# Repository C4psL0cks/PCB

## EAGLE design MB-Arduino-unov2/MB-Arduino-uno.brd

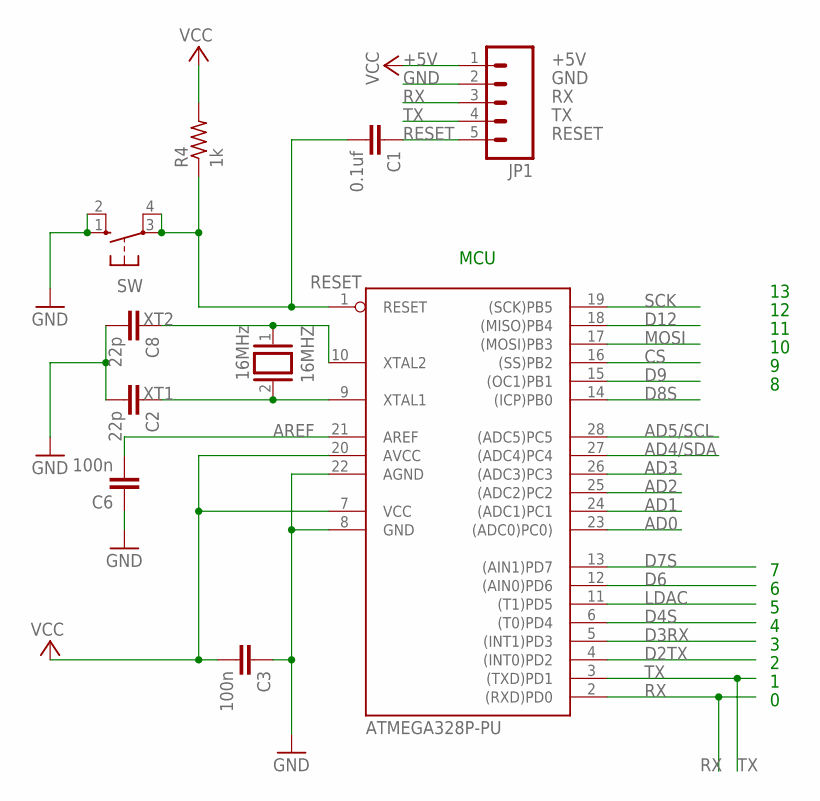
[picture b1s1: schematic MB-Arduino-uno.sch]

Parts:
16MHZ: 16MHz; QS
C1: 0.1uf; C2.5-2
C2, C8: 22p; C2.5-2
C3, C6: 100n; C2.5-2
IC: ATMEGA328P-PU; DIL28-3
JP1: M05PTH; 1X05
R4: 1k; 0204/7
SW: 10-XX; B3F-10XX

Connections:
+5V: C3.2, IC.7 (VCC), IC.20 (AVCC), JP1.1, R4.2
AD0: IC.23 ((ADC0)PC0))
AD1: IC.24 ((ADC1)PC1)
AD2: IC.25 ((ADC2)PC2)
AD3: IC.26 ((ADC3)PC3)
AD4/SDA: IC.27 ((ADC4)PC4)
AD5/SCL: IC.28 ((ADC5)PC5)
AREF: C6.2, IC.21 (AREF)
CS: IC.16 ((SS)PB2)
D2TX: IC.4 ((INT0)PD2)
D3RX: IC.5 ((INT1)PD3)
D4S: IC.6 ((T0)PD4)
D6: IC.12 ((AIN0)PD6)
D7S: IC.13 ((AIN1)PD7)
D8S: IC.14 ((ICP)PB0)
D9: IC.15 ((OC1)PB1)
D12: IC.18 ((MISO)PB4)
GND: C2.2, C3.1, C6.1, C8.2, IC.8 (GND), IC.22 (AGND), JP1.2, SW.1 (S), SW.2 (S1)
LDAC: IC.11 ((T1)PD5)
MOSI: IC.17 ((MOSI)PB3)
RESET: C1.1, C1.2, IC.1 (RESET), JP1.5, R4.1, SW.3, SW.4 (P1)
RX: IC.2 ((RXD)PD0), JP1.3
SCK: IC.19 ((SCK)PB5)
TX: IC.3 ((TXD)PD1), JP1.4
XT1: 16MHZ.2, C2.1, IC.9 (XTAL1)
XT2: 16MHZ.1, C8.1, IC.10 (XTAL2)

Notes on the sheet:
MCU

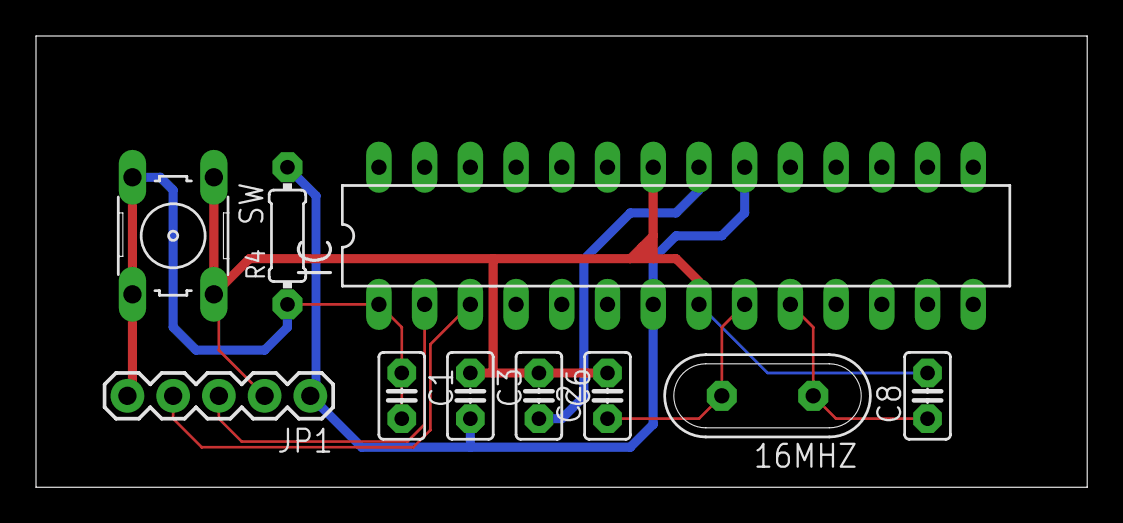
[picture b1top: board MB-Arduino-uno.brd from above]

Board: 2 copper layers, 58.4 x 25.1 mm, 10 parts (0 on the bottom side), 8 nets.

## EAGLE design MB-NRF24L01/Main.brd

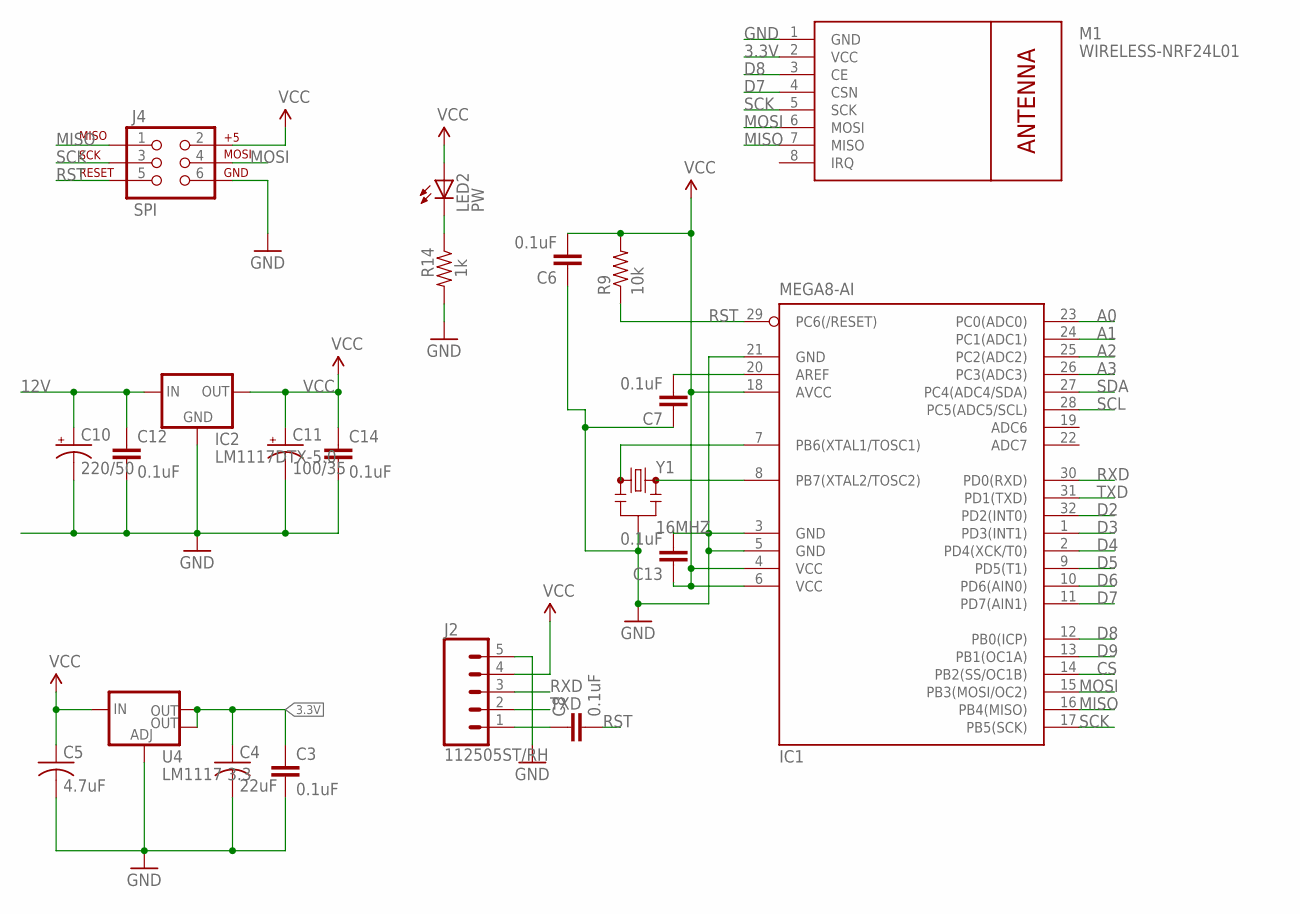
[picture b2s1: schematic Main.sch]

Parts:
C3, C6, C7, C8, C12, C13, C14: 0.1uF; 0805
C4: 22uF; C1206
C5: 4.7uF; C1206
C10: 220/50; 153CLV-1010
C11: 100/35; 153CLV-0605
IC1: MEGA8-AI; TQFP32-08
IC2: LM1117DTX-5.0; TO252
J2: 112505ST/RH; JST-5-PTH
J4: SPI; 2X3
LED2: PW; LED3MM
M1: WIRELESS-NRF24L01
R9: 10k; 0805
R14: 1k; 0805
U4: LM1117 3.3; SOT223
Y1: 16MHZ; RESONATOR-SMD

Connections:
3.3V: C3.1, C4.1, M1.2 (VCC), U4.2 (OUT), U4.4 (OUT)
12V: C10.+, C12.1, IC2.2 (IN)
A0: IC1.23 (PC0(ADC0))
A1: IC1.24 (PC1(ADC1))
A2: IC1.25 (PC2(ADC2))
A3: IC1.26 (PC3(ADC3))
CS: IC1.14 (PB2(SS/OC1B))
D2: IC1.32 (PD2(INT0))
D3: IC1.1 (PD3(INT1))
D4: IC1.2 (PD4(XCK/T0))
D5: IC1.9 (PD5(T1))
D6: IC1.10 (PD6(AIN0))
D7: IC1.11 (PD7(AIN1)), M1.4 (CSN)
D8: IC1.12 (PB0(ICP)), M1.3 (CE)
D9: IC1.13 (PB1(OC1A))
GND: C3.2, C4.2, C5.2, C6.1, C7.1, C10.-, C11.-, C12.2, C13.2, C14.2, IC1.3 (GND), IC1.5 (GND), IC1.21 (GND), IC2.1 (GND), J2.5, J4.6, M1.1 (GND), R14.2, U4.1 (ADJ), Y1.2
MISO: IC1.16 (PB4(MISO)), J4.1, M1.7 (MISO)
MOSI: IC1.15 (PB3(MOSI/OC2)), J4.4, M1.6 (MOSI)
unnamed: IC1.8 (PB7(XTAL2/TOSC2)), Y1.3
unnamed: IC1.7 (PB6(XTAL1/TOSC1)), Y1.1
unnamed: C7.2, IC1.20 (AREF)
unnamed: C8.1, J2.1
unnamed: LED2.K (C), R14.1
RST: C8.2, IC1.29 (PC6(/RESET)), J4.5, R9.1
RXD: IC1.30 (PD0(RXD)), J2.3
SCK: IC1.17 (PB5(SCK)), J4.3, M1.5 (SCK)
SCL: IC1.28 (PC5(ADC5/SCL))
SDA: IC1.27 (PC4(ADC4/SDA))
TXD: IC1.31 (PD1(TXD)), J2.2
VCC: C5.1, C6.2, C11.+, C13.1, C14.1, IC1.4 (VCC), IC1.6 (VCC), IC1.18 (AVCC), IC2.TAB (OUT), J2.4, J4.2, LED2.A, R9.2, U4.3 (IN)

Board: 2 copper layers, 21 parts (0 on the bottom side), 17 nets, no tracks yet.

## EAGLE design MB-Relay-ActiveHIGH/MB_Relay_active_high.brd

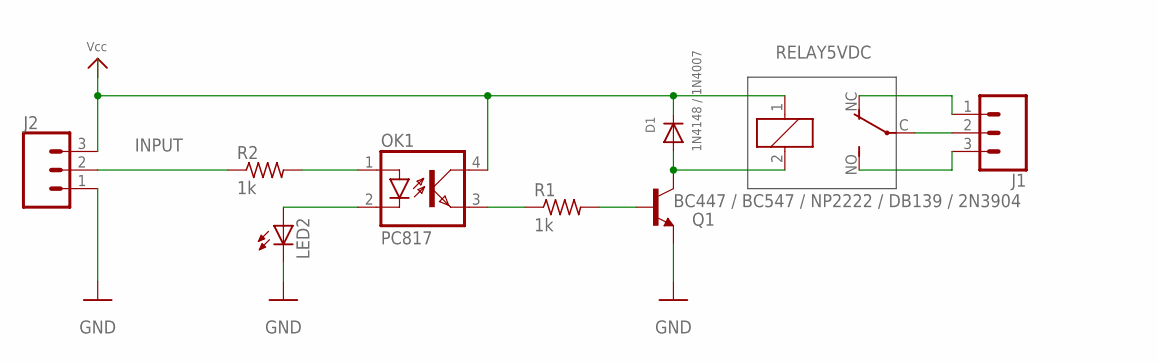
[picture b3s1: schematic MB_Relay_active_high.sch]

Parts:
D1: 1N4148 / 1N4007; DO-1N4148
J1, J2: CONN_03; 1X03
LED2: LED3MM
OK1: PC817; DIL04
Q1: BC447 / BC547 / NP2222 / DB139 / 2N3904; TO92-EBC
R1, R2: 1k; 0204/7
RELAY5VDC: RELAY 5VDC; CQ1

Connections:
GND: J2.1, LED2.K (C), Q1.E
INPUT: J2.2, R2.1
unnamed: OK1.1 (A), R2.2
unnamed: LED2.A, OK1.2 (C)
unnamed: OK1.3 (EMIT), R1.1
unnamed: D1.A, Q1.C, RELAY5VDC.2
unnamed: J1.1, RELAY5VDC.NC (O)
unnamed: J1.3, RELAY5VDC.NO (S)
unnamed: J1.2, RELAY5VDC.C
unnamed: Q1.B, R1.2
RELAY_POWER_5V: D1.C, J2.3, OK1.4 (COL), RELAY5VDC.1

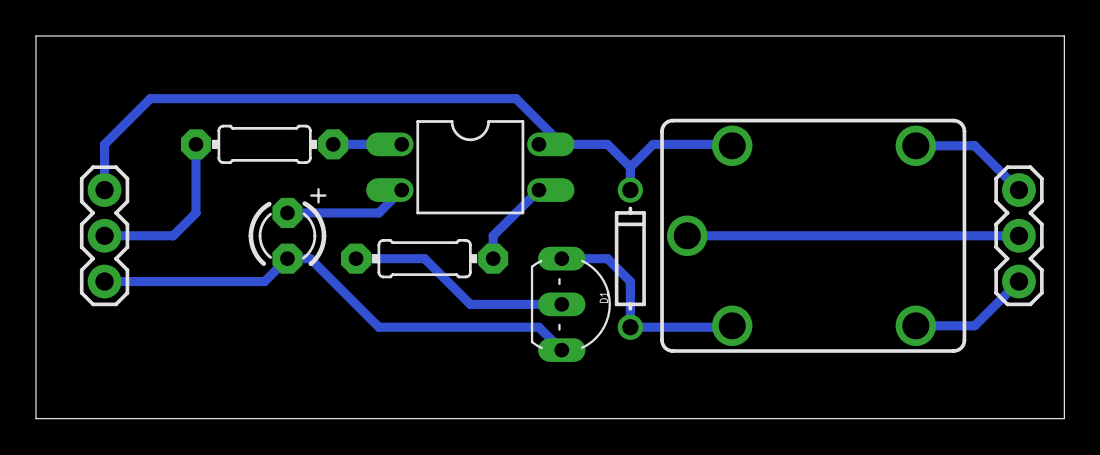
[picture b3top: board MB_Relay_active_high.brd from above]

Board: 2 copper layers, 57.1 x 21.3 mm, 9 parts (0 on the bottom side), 11 nets.

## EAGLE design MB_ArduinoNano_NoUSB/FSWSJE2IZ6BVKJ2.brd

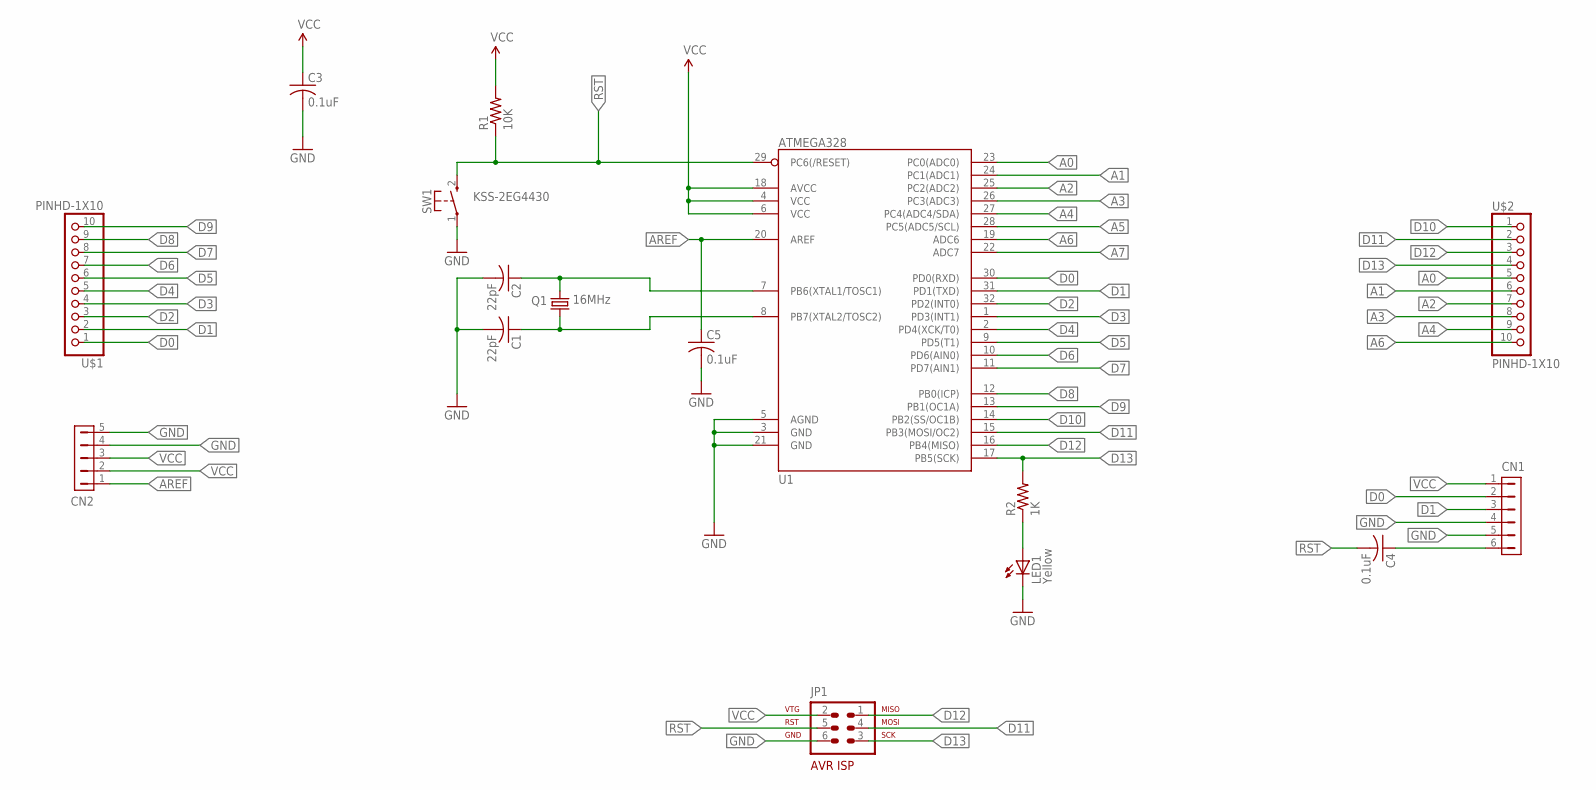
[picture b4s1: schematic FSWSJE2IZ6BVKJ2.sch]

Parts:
C1, C2: 22pF; C1206
C3, C4, C5: 0.1uF; C0805
CN1: HDR-1X6-SIP-100; SIP-100-6V
CN2: HDR-1X5-SIP-100; SIP-100-5V
JP1: AVR-ISP-6
LED1: Yellow; CHIP-LED0805
Q1: 16MHz; HC49/S
R1: 10K; R1206
R2: 1K; R1206
SW1: KSS-2EG4430
U1: ATMEGA328; TQFP32-08
U$1, U$2: PINHD-1X10; 1X10-BIG

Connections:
A0: U1.23 (PC0(ADC0)), U$2.5
A1: U1.24 (PC1(ADC1)), U$2.6
A2: U1.25 (PC2(ADC2)), U$2.7
A3: U1.26 (PC3(ADC3)), U$2.8
A4: U1.27 (PC4(ADC4/SDA)), U$2.9
A5: U1.28 (PC5(ADC5/SCL))
A6: U1.19 (ADC6), U$2.10
A7: U1.22 (ADC7)
AREF: C5.1, CN2.1, U1.20 (AREF)
D0: CN1.2, U1.30 (PD0(RXD)), U$1.1
D1: CN1.3, U1.31 (PD1(TXD)), U$1.2
D2: U1.32 (PD2(INT0)), U$1.3
D3: U1.1 (PD3(INT1)), U$1.4
D4: U1.2 (PD4(XCK/T0)), U$1.5
D5: U1.9 (PD5(T1)), U$1.6
D6: U1.10 (PD6(AIN0)), U$1.7
D7: U1.11 (PD7(AIN1)), U$1.8
D8: U1.12 (PB0(ICP)), U$1.9
D9: U1.13 (PB1(OC1A)), U$1.10
D10: U1.14 (PB2(SS/OC1B)), U$2.1
D11: JP1.4, U1.15 (PB3(MOSI/OC2)), U$2.2
D12: JP1.1, U1.16 (PB4(MISO)), U$2.3
D13: JP1.3, R2.2, U1.17 (PB5(SCK)), U$2.4
GND: C1.2, C2.2, C3.2, C5.2, CN1.4, CN1.5, CN2.4, CN2.5, JP1.6, LED1.C, SW1.1, U1.3 (GND), U1.5 (AGND), U1.21 (GND)
unnamed: C4.1, CN1.6
unnamed: C2.1, Q1.2, U1.7 (PB6(XTAL1/TOSC1))
unnamed: C1.1, Q1.1, U1.8 (PB7(XTAL2/TOSC2))
unnamed: LED1.A, R2.1
RST: C4.2, JP1.5, R1.1, SW1.2 (S), U1.29 (PC6(/RESET))
VCC: C3.1, CN1.1, CN2.2, CN2.3, JP1.2, R1.2, U1.4 (VCC), U1.6 (VCC), U1.18 (AVCC)

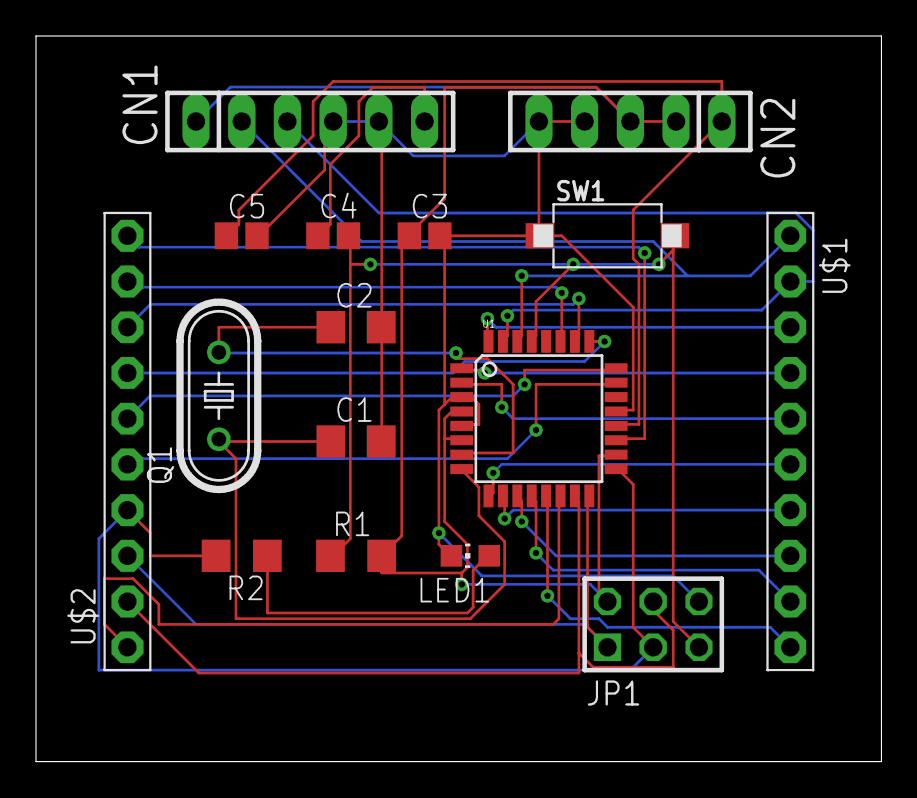
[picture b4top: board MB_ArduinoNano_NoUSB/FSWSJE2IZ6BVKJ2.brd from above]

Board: 2 copper layers, 47.0 x 40.3 mm, 16 parts (0 on the bottom side), 28 nets.

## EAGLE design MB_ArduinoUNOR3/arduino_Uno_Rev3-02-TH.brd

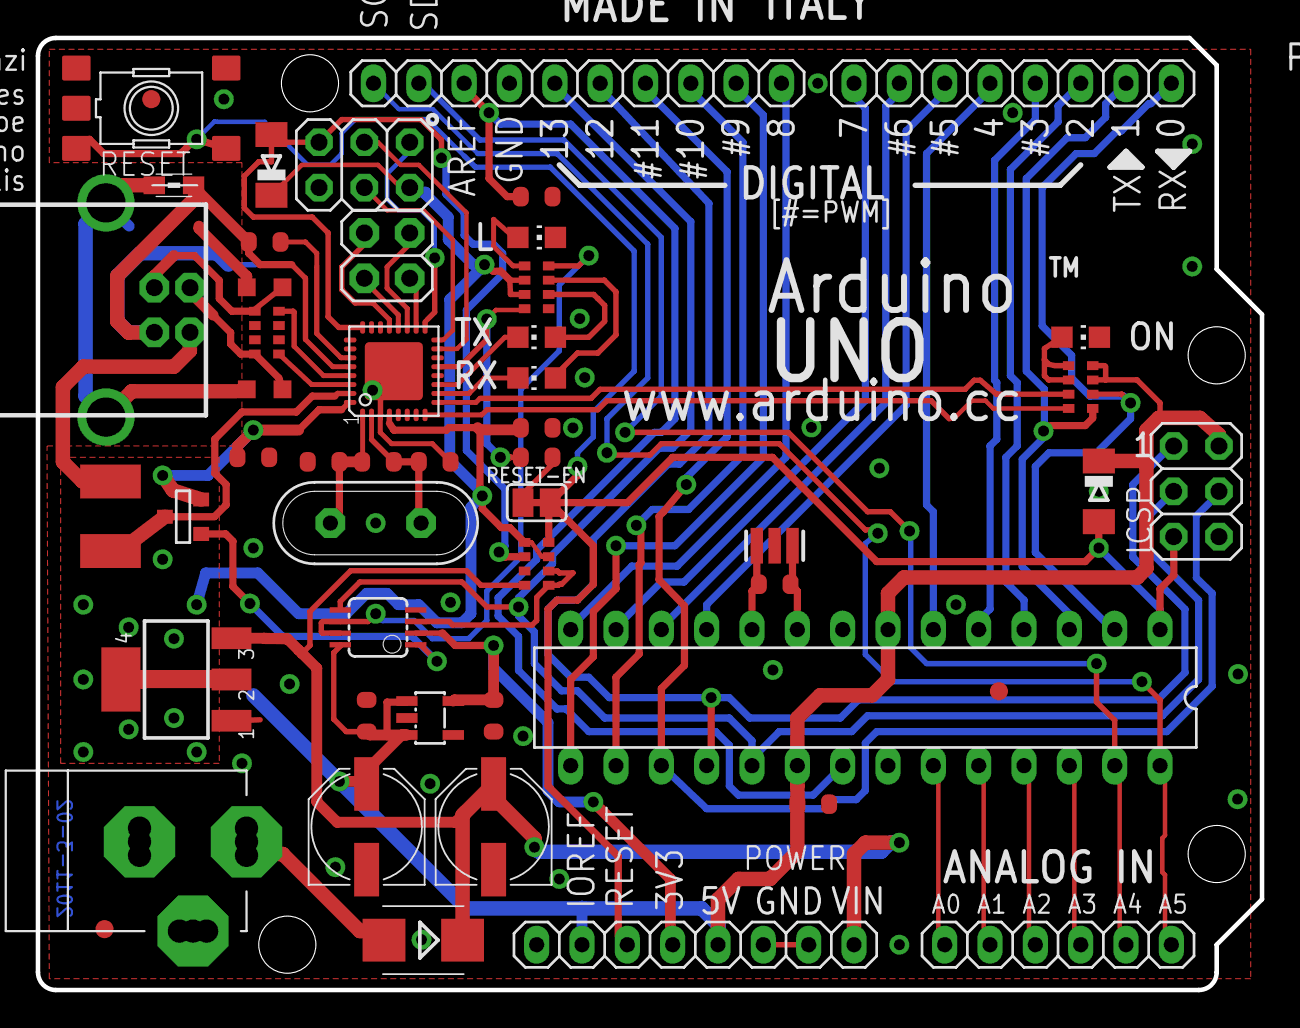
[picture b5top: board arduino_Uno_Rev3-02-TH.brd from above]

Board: 2 copper layers, 68.6 x 53.3 mm, 53 parts (1 on the bottom side), 60 nets.

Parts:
AD: 6x1F-H8.5; 1X06
C1, C2, C4, C5, C6, C7: 100n; C0603-ROUND
C3, C8: 1u; C0603-ROUND
C9, C11: 22p; C0603-ROUND
D1: M7; SMB
D2, D3: CD1206-S01575; MINIMELF
F1: MF-MSMF050-2 500mA; L1812
FD1, FD2, FD3: FIDUCIALMOUNT; FIDUCIA-MOUNT
GROUND: SJ
ICSP, ICSP1: 3x2 M; 2X03
IOH: 10x1F-H8.5; 1X10
IOL: 8x1F-H8.5; 1X08
JP2: 2x2 M - NM; 2X02
L: YELLOW; CHIP-LED0805
L1: BLM21; 0805
ON: GREEN; CHIP-LED0805
PC1, PC2: 47u; PANASONIC_D
POWER: 8x1F-H8.5; 1X08
R1, R2: 1M; R0603-ROUND
RESET: TS42031-160R-TR-7260; TS42
RESET-EN: SJ
RN1: 10K; CAY16
RN2, RN4: 1K; CAY16
RN3: 22R; CAY16
RX: YELLOW; CHIP-LED0805
T1: FDN340P; SOT-23
TX: YELLOW; CHIP-LED0805
U1: NCP1117ST50T3G; SOT223
U2: LP2985-33DBVR; SOT23-DBV
U3: ATMEGA16U2-MU(R); MLF32
U5: LMV358IDGKR; MSOP08
U$1: DISCLAIMER
X1: POWERSUPPLY_DC21MMX; POWERSUPPLY_DC-21MM
X2: USB-B_TH; PN61729
Y1: 16MHz; QS
Y2: CSTCE16M0V53-R0 16MHZ; RESONATOR
Z1, Z2: CG0603MLC-05E; CT/CN0603
ZU4: ATMEGA328P-PU; DIL28-3

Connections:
+3V3: C3.2, POWER.4, U2.5, U5.2
+5V: C1.2, C2.2, C6.2, C7.1, D2.C, D3.C, ICSP.2, ICSP1.2, PC2.+, POWER.2, POWER.5, RN1.3, RN1.5, RN2.2, RN2.3, RN4.3, RN4.4, T1.2, U1.2, U1.4, U2.1, U2.3, U3.4, U3.32, U5.8, ZU4.7, ZU4.20
AD0: AD.1, ZU4.23
AD1: AD.2, ZU4.24
AD2: AD.3, ZU4.25
AD3: AD.4, ZU4.26
AD4/SDA: AD.5, IOH.9, ZU4.27
AD5/SCL: AD.6, IOH.10, ZU4.28
AREF: C4.2, IOH.8, ZU4.21
CMP: RN1.1, RN1.2, U5.3
D+: RN3.5, X2.3, Z1.1
D-: RN3.8, X2.2, Z2.1
DTR: C5.1, RN2.4, U3.13
GATE_CMD: T1.3, U5.1
GND: C1.1, C2.1, C3.1, C4.1, C6.1, C7.2, C9.2, C11.2, GROUND.1, ICSP.6, ICSP1.6, IOH.7, L.C, ON.C, PC1.-, PC2.-, POWER.6, POWER.7, RESET.1, RESET.2, RN1.7, RN2.5, U1.1, U2.2, U3.3, U3.33, U5.4, X1.1, X1.3, Y2.2, ZU4.8, ZU4.22
IO0: IOL.1, RN4.2, ZU4.2
IO1: IOL.2, RN4.1, ZU4.3
IO2: IOL.3, ZU4.4
IO3: IOL.4, ZU4.5
IO4: IOL.5, ZU4.6
IO5: IOL.6, ZU4.11
IO6: IOL.7, ZU4.12
IO7: IOL.8, ZU4.13
IO8: IOH.1, ZU4.14
IO9: IOH.2, ZU4.15
L13: RN2.8, U5.6, U5.7
M8RXD: RN4.7, U3.9
M8TXD: RN4.8, U3.8
MISO: ICSP.1, IOH.5, ZU4.18
MISO2: ICSP1.1, U3.17
MOSI: ICSP.4, IOH.4, ZU4.17
MOSI2: ICSP1.4, U3.16
unnamed: L.A, RN2.1
unnamed: ON.A, RN4.5, RN4.6
unnamed: RN2.7, RX.A
unnamed: RN2.6, TX.A
PB4: JP2.1, U3.18
PB5: JP2.3, U3.19
PB6: JP2.2, U3.20
PB7: JP2.4, U3.21
PWRIN: D1.A, X1.2
RD+: RN3.4, U3.29
RD-: RN3.1, U3.30
RESET: C5.2, D2.A, ICSP.5, POWER.3, RESET.3, RESET.4, RESET-EN.1, RESET-EN.2, RN1.4, ZU4.1
RESET2: D3.A, ICSP1.5, RN1.6, U3.24
RXLED: RX.C, U3.10
SCK: ICSP.3, IOH.6, U5.5, ZU4.19
SCK2: ICSP1.3, U3.15
SS: IOH.3, ZU4.16
TP_VUCAP: C8.1, U3.27
TXLED: TX.C, U3.11
UGND: C8.2, GROUND.2, L1.1, U3.28, X2.4
USBVCC: F1.1, T1.1, U3.31
USHIELD: L1.2, X2.P$1, X2.P$2, Z1.2, Z2.2
VIN: D1.C, PC1.+, POWER.8, RN1.8, U1.3
XT1: C9.1, R1.1, U3.1, Y1.2
XT2: C11.1, R1.2, U3.2, Y1.1
XTAL1: R2.1, Y2.3, ZU4.9
XTAL2: R2.2, Y2.1, ZU4.10
XUSB: F1.2, X2.1

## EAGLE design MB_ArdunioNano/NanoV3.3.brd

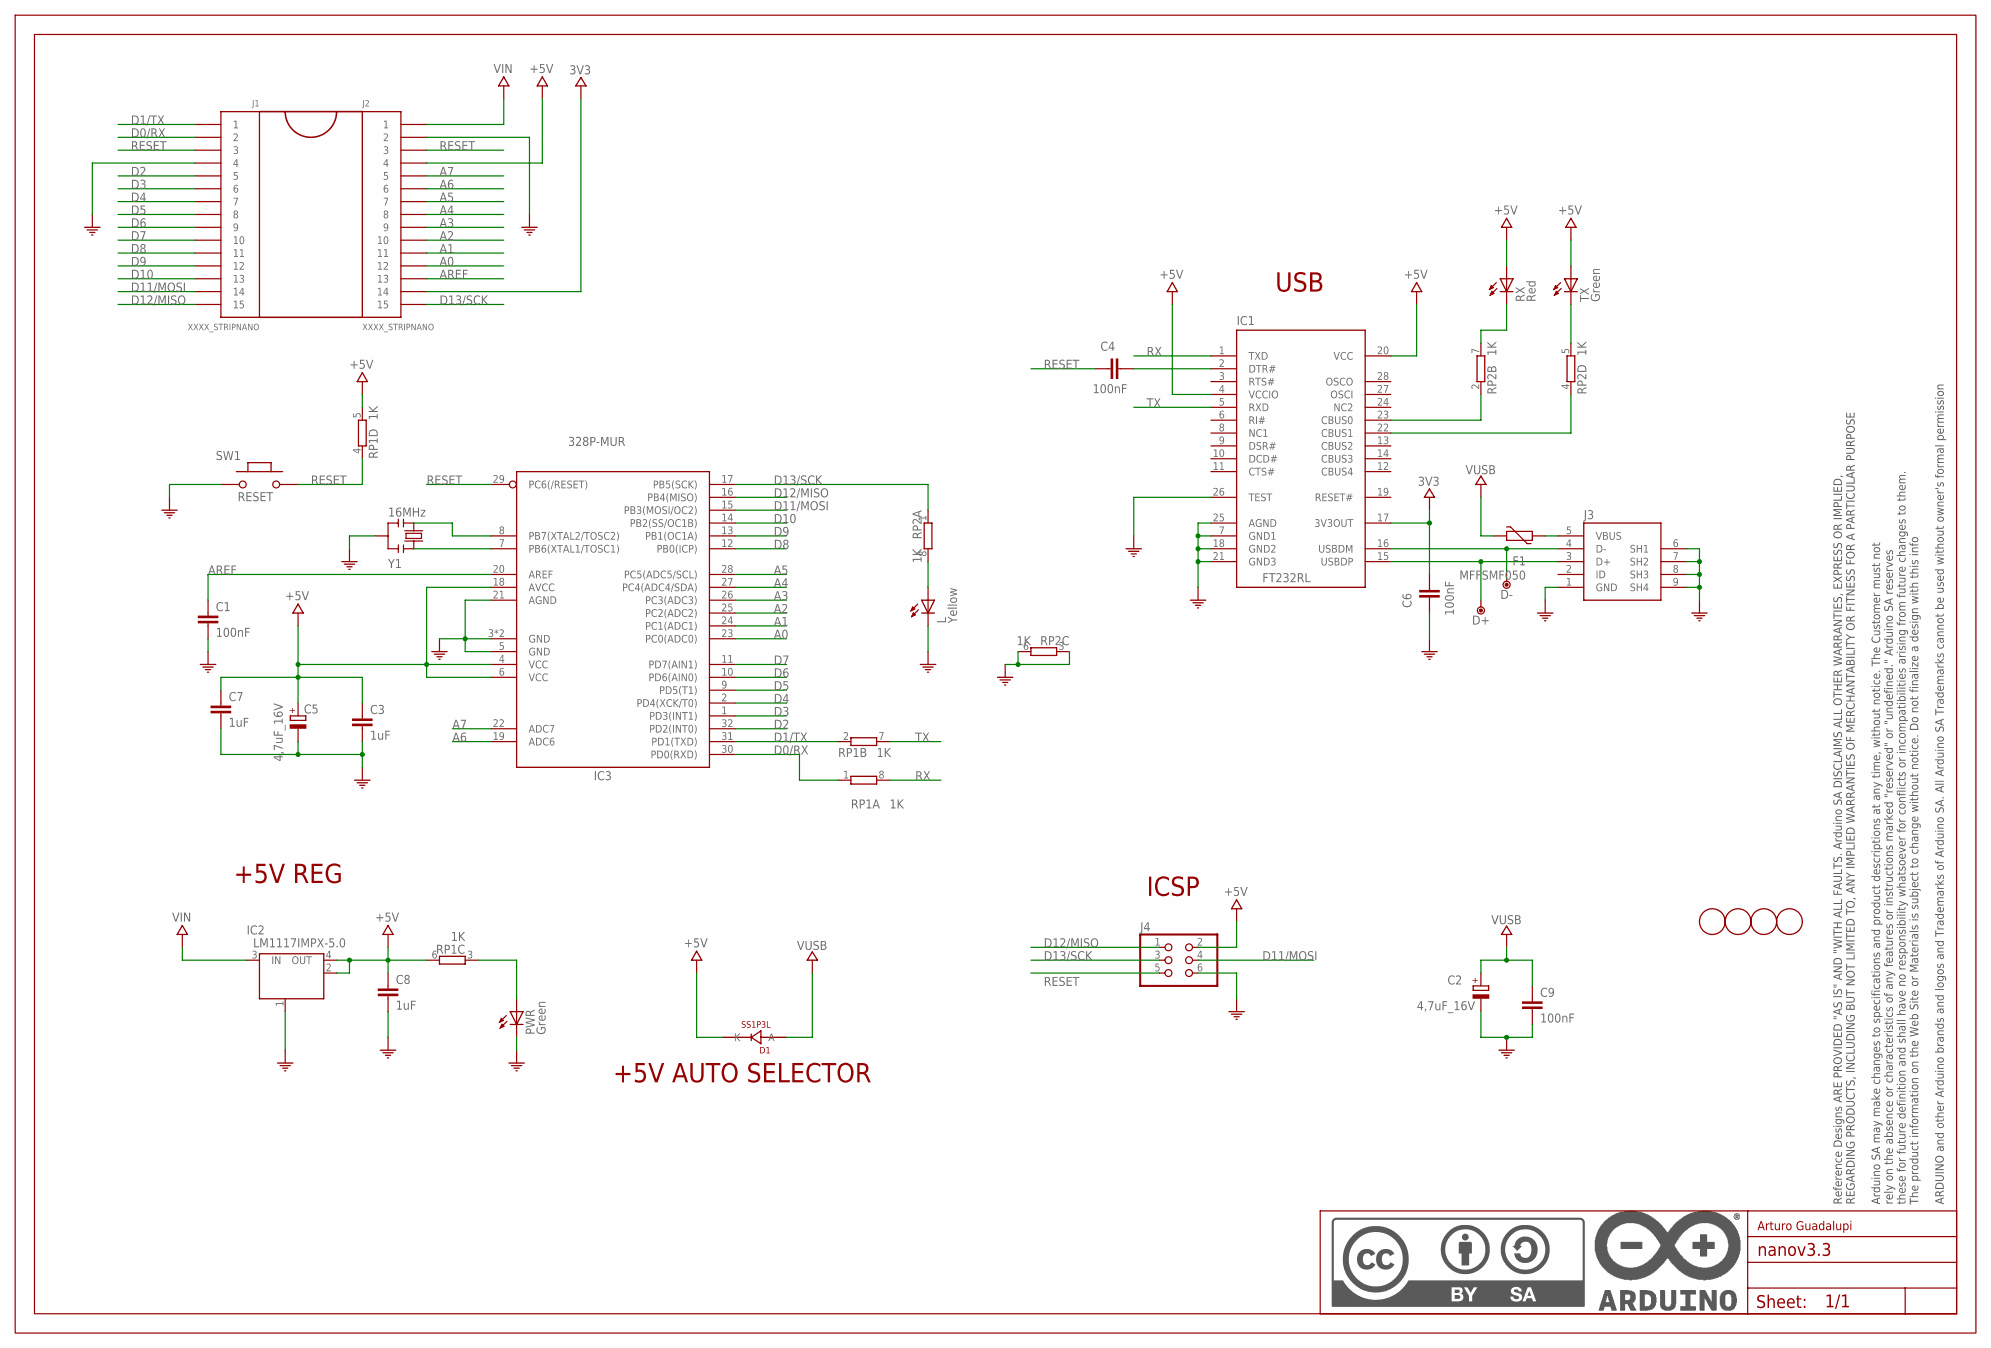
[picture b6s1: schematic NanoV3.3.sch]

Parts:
C1, C4, C6, C9: 100nF; C0603-ROUND
C2, C5: 4,7uF_16V; TAN-A
C3, C7, C8: 1uF; C0603-ROUND
D1: SS1P3L; DO220AAL
D+: DNP; TP-1.00MM
D-: DNP; TP-1.00MM
F1: MFFSMF050; 0603-1608X90N
FRAME1: DNP; FRAME
IC1: FT232RL; SSOP28
IC2: LM1117IMPX-5.0; LINEAR_SOT223
IC3: 328P-MUR; VQFN32
J1, J2: XXXX_STRIPNANO; HEAD15-NOSS
J3: 0219_14850; USB-MINI-B_2
J4: 0114_PH254-203DF118A00V; 2X03
L: Yellow; CHIPLED_0805
PWR: Green; CHIPLED_0805
RP1, RP2: 1K; CAY16
RX: Red; CHIPLED_0805
SW1: RESET; SMD_157SW
TX: Green; CHIPLED_0805
U$4, U$5, U$53, U$54: DNP; FD-1-1.5
Y1: 16MHz; RESONATOR

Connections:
3V3: C6.2, IC1.17 (3V3OUT), J2.14
+5V: C3.1, C5.1 (+), C7.1, C8.1, D1.P$1 (K), IC1.4 (VCCIO), IC1.20 (VCC), IC2.2 (OUT), IC2.4 (OUT), IC3.4 (VCC), IC3.6 (VCC), IC3.18 (AVCC), J2.4, J4.2, RP1.5 (2), RP1.6 (2), RX.A, TX.A
A0: IC3.23 (PC0(ADC0)), J2.12
A1: IC3.24 (PC1(ADC1)), J2.11
A2: IC3.25 (PC2(ADC2)), J2.10
A3: IC3.26 (PC3(ADC3)), J2.9
A4: IC3.27 (PC4(ADC4/SDA)), J2.8
A5: IC3.28 (PC5(ADC5/SCL)), J2.7
A6: IC3.19 (ADC6), J2.6
A7: IC3.22 (ADC7), J2.5
AREF: C1.1, IC3.20 (AREF), J2.13
COM: C1.2, C2.2 (-), C3.2, C5.2 (-), C6.1, C7.2, C8.2, C9.2, IC1.7 (GND1), IC1.18 (GND2), IC1.21 (GND3), IC1.25 (AGND), IC1.26 (TEST), IC2.1 (GND/ADJ), IC3.3 (GND), IC3.5 (GND), IC3.21 (AGND), IC3.33 (GND), J1.4, J2.2, J3.1 (GND), J3.6 (SH1), J3.7 (SH2), J3.8 (SH3), J3.9 (SH4), J4.6, L.C, PWR.C, RP2.3 (1), RP2.6 (2), SW1.1, Y1.2
D0/RX: IC3.30 (PD0(RXD)), J1.2, RP1.1
D1/TX: IC3.31 (PD1(TXD)), J1.1, RP1.2 (1)
D2: IC3.32 (PD2(INT0)), J1.5
D3: IC3.1 (PD3(INT1)), J1.6
D4: IC3.2 (PD4(XCK/T0)), J1.7
D5: IC3.9 (PD5(T1)), J1.8
D6: IC3.10 (PD6(AIN0)), J1.9
D7: IC3.11 (PD7(AIN1)), J1.10
D8: IC3.12 (PB0(ICP)), J1.11
D9: IC3.13 (PB1(OC1A)), J1.12
D10: IC3.14 (PB2(SS/OC1B)), J1.13
D11/MOSI: IC3.15 (PB3(MOSI/OC2)), J1.14, J4.4
D12/MISO: IC3.16 (PB4(MISO)), J1.15, J4.1
D13/SCK: IC3.17 (PB5(SCK)), J2.15, J4.3, RP2.1
unnamed: IC3.8 (PB7(XTAL2/TOSC2)), Y1.3
unnamed: IC3.7 (PB6(XTAL1/TOSC1)), Y1.1
unnamed: PWR.A, RP1.3 (1)
unnamed: C4.2, IC1.2 (DTR#)
unnamed: D+.X, IC1.15 (USBDP), J3.3 (D+)
unnamed: D-.X, IC1.16 (USBDM), J3.4 (D-)
unnamed: L.A, RP2.8 (2)
unnamed: IC1.23 (CBUS0), RP2.2 (1)
unnamed: IC1.22 (CBUS1), RP2.4 (1)
unnamed: RP2.5 (2), TX.C
unnamed: F1.2, J3.5 (VBUS)
unnamed: RP2.7 (2), RX.C
RESET: C4.1, IC3.29 (PC6(/RESET)), J1.3, J2.3, J4.5, RP1.4 (1), SW1.2
RX: IC1.1 (TXD), RP1.8 (2)
TX: IC1.5 (RXD), RP1.7 (2)
VIN: IC2.3 (IN), J2.1
VUSB: C2.1 (+), C9.1, D1.P$2 (A), F1.1

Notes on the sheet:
+5V REG
ICSP
USB
+5V AUTO SELECTOR
Arturo Guadalupi

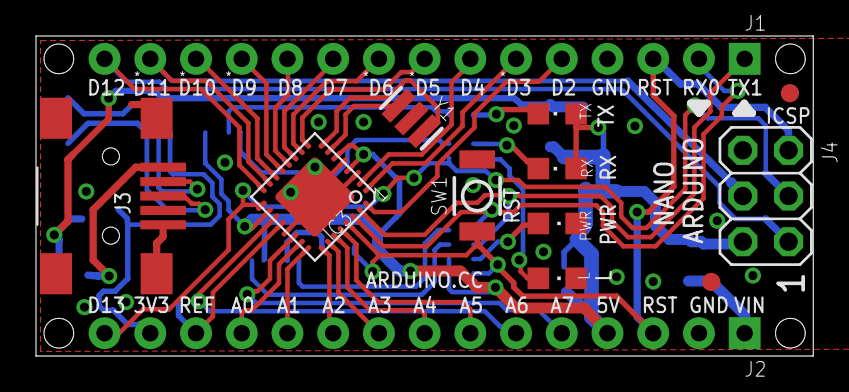
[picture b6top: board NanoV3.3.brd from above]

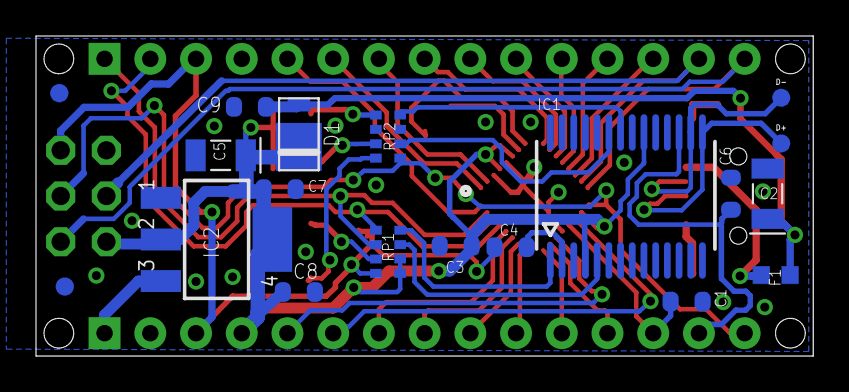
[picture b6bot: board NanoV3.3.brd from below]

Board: 2 copper layers, 43.2 x 17.8 mm, 33 parts (17 on the bottom side), 43 nets.

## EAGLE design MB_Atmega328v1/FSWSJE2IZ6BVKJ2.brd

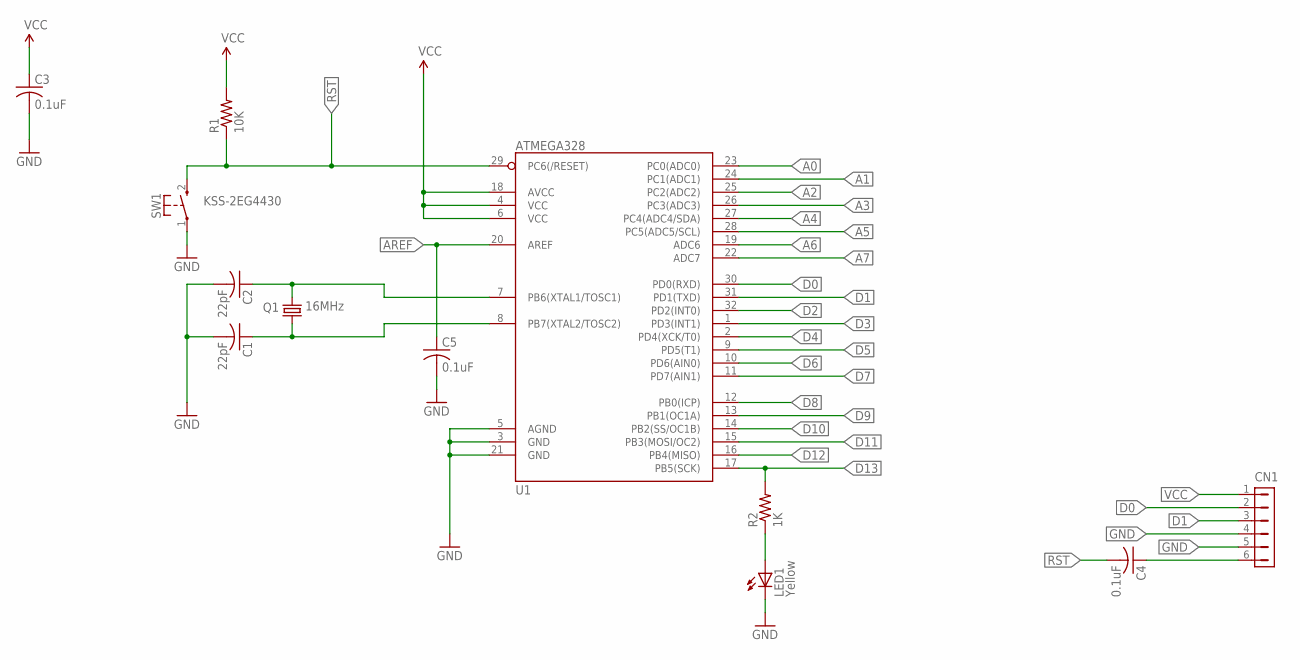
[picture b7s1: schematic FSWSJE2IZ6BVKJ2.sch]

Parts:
C1, C2: 22pF; C1206
C3, C4, C5: 0.1uF; C0805
CN1: HDR-1X6-SIP-100; SIP-100-6V
LED1: Yellow; CHIP-LED0805
Q1: 16MHz; HC49/S
R1: 10K; R1206
R2: 1K; R1206
SW1: KSS-2EG4430
U1: ATMEGA328; TQFP32-08

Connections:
A0: U1.23 (PC0(ADC0))
A1: U1.24 (PC1(ADC1))
A2: U1.25 (PC2(ADC2))
A3: U1.26 (PC3(ADC3))
A4: U1.27 (PC4(ADC4/SDA))
A5: U1.28 (PC5(ADC5/SCL))
A6: U1.19 (ADC6)
A7: U1.22 (ADC7)
AREF: C5.1, U1.20 (AREF)
D0: CN1.2, U1.30 (PD0(RXD))
D1: CN1.3, U1.31 (PD1(TXD))
D2: U1.32 (PD2(INT0))
D3: U1.1 (PD3(INT1))
D4: U1.2 (PD4(XCK/T0))
D5: U1.9 (PD5(T1))
D6: U1.10 (PD6(AIN0))
D7: U1.11 (PD7(AIN1))
D8: U1.12 (PB0(ICP))
D9: U1.13 (PB1(OC1A))
D10: U1.14 (PB2(SS/OC1B))
D11: U1.15 (PB3(MOSI/OC2))
D12: U1.16 (PB4(MISO))
D13: R2.2, U1.17 (PB5(SCK))
GND: C1.2, C2.2, C3.2, C5.2, CN1.4, CN1.5, LED1.C, SW1.1, U1.3 (GND), U1.5 (AGND), U1.21 (GND)
unnamed: C4.1, CN1.6
unnamed: C2.1, Q1.2, U1.7 (PB6(XTAL1/TOSC1))
unnamed: C1.1, Q1.1, U1.8 (PB7(XTAL2/TOSC2))
unnamed: LED1.A, R2.1
RST: C4.2, R1.1, SW1.2 (S), U1.29 (PC6(/RESET))
VCC: C3.1, CN1.1, R1.2, U1.4 (VCC), U1.6 (VCC), U1.18 (AVCC)

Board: 2 copper layers, 12 parts (0 on the bottom side), 11 nets, no tracks yet.

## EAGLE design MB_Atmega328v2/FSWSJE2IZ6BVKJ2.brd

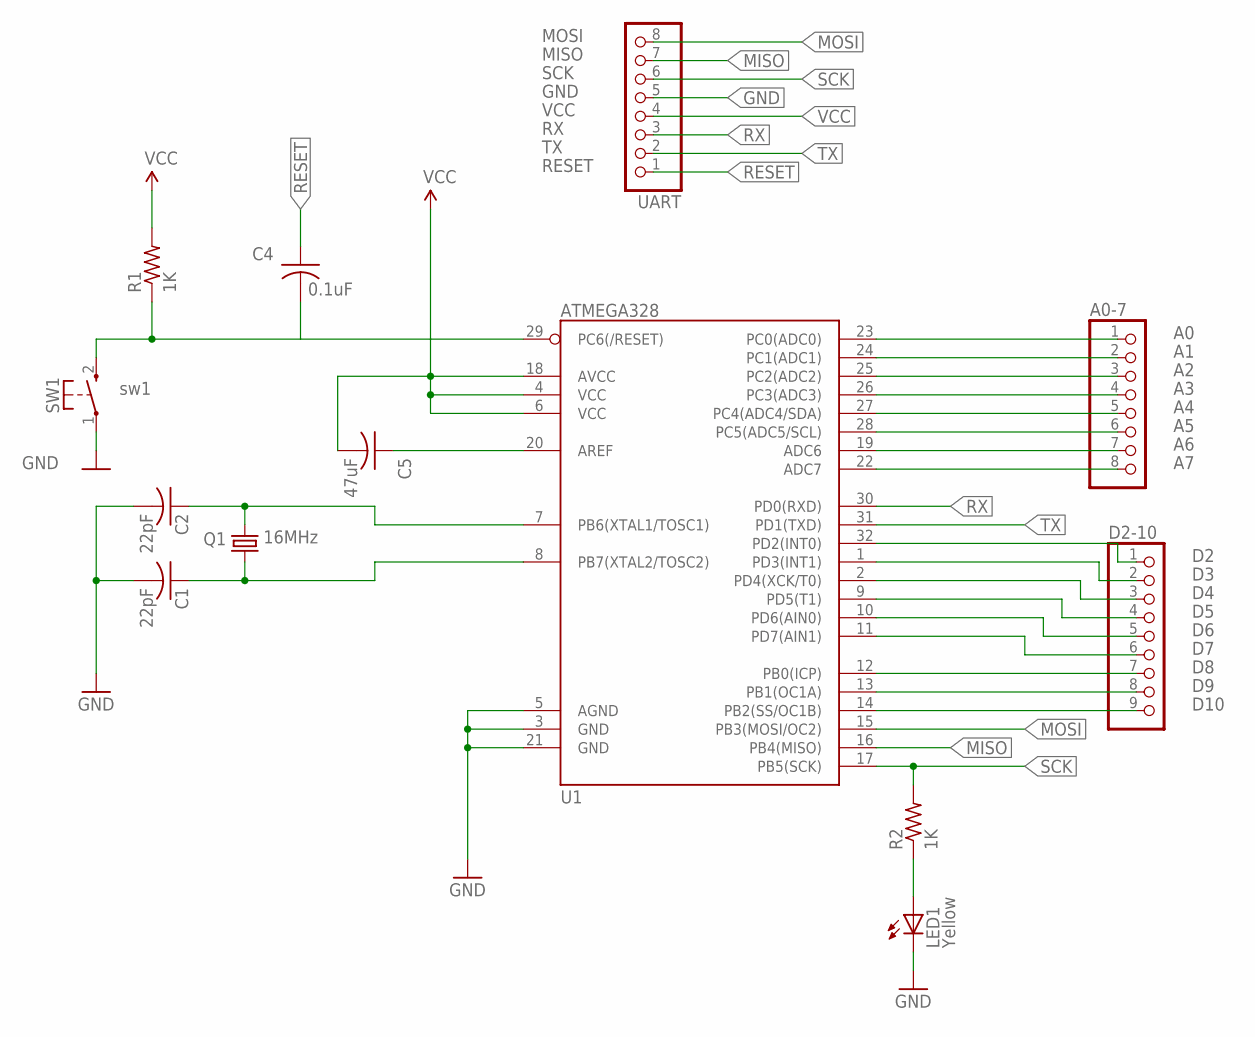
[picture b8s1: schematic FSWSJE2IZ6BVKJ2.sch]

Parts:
A0-7: PINHD-1X8CLEANBIG; 1X08-CLEANBIG
C1, C2: 22pF; C1206
C4: 0.1uF; C0805
C5: 47uF; C0805
D2-10: PINHD-1X9; 1X09-BIG
LED1: Yellow; CHIP-LED0805
Q1: 16MHz; HC49/S
R1, R2: 1K; R1206
SW1: sw1; KSS-2EG4430
U1: ATMEGA328; TQFP32-08
UART: PINHD-1X8CLEANBIG; 1X08-CLEANBIG

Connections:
A0: A0-7.1, U1.23 (PC0(ADC0))
A1: A0-7.2, U1.24 (PC1(ADC1))
A2: A0-7.3, U1.25 (PC2(ADC2))
A3: A0-7.4, U1.26 (PC3(ADC3))
A4: A0-7.5, U1.27 (PC4(ADC4/SDA))
A5: A0-7.6, U1.28 (PC5(ADC5/SCL))
A6: A0-7.7, U1.19 (ADC6)
A7: A0-7.8, U1.22 (ADC7)
D2: D2-10.1, U1.32 (PD2(INT0))
D3: D2-10.2, U1.1 (PD3(INT1))
D4: D2-10.3, U1.2 (PD4(XCK/T0))
D5: D2-10.4, U1.9 (PD5(T1))
D6: D2-10.5, U1.10 (PD6(AIN0))
D7: D2-10.6, U1.11 (PD7(AIN1))
D8: D2-10.7, U1.12 (PB0(ICP))
D9: D2-10.8, U1.13 (PB1(OC1A))
D10: D2-10.9, U1.14 (PB2(SS/OC1B))
GND: C1.2, C2.2, LED1.C, SW1.1, U1.3 (GND), U1.5 (AGND), U1.21 (GND), UART.5
MISO: U1.16 (PB4(MISO)), UART.7
MOSI: U1.15 (PB3(MOSI/OC2)), UART.8
unnamed: C5.1, U1.20 (AREF)
unnamed: C2.1, Q1.2, U1.7 (PB6(XTAL1/TOSC1))
unnamed: C1.1, Q1.1, U1.8 (PB7(XTAL2/TOSC2))
unnamed: LED1.A, R2.1
RESET: C4.1, UART.1
RST: C4.2, R1.1, SW1.2 (S), U1.29 (PC6(/RESET))
RX: U1.30 (PD0(RXD)), UART.3
SCK: R2.2, U1.17 (PB5(SCK)), UART.6
TX: U1.31 (PD1(TXD)), UART.2
VCC: C5.2, R1.2, U1.4 (VCC), U1.6 (VCC), U1.18 (AVCC), UART.4

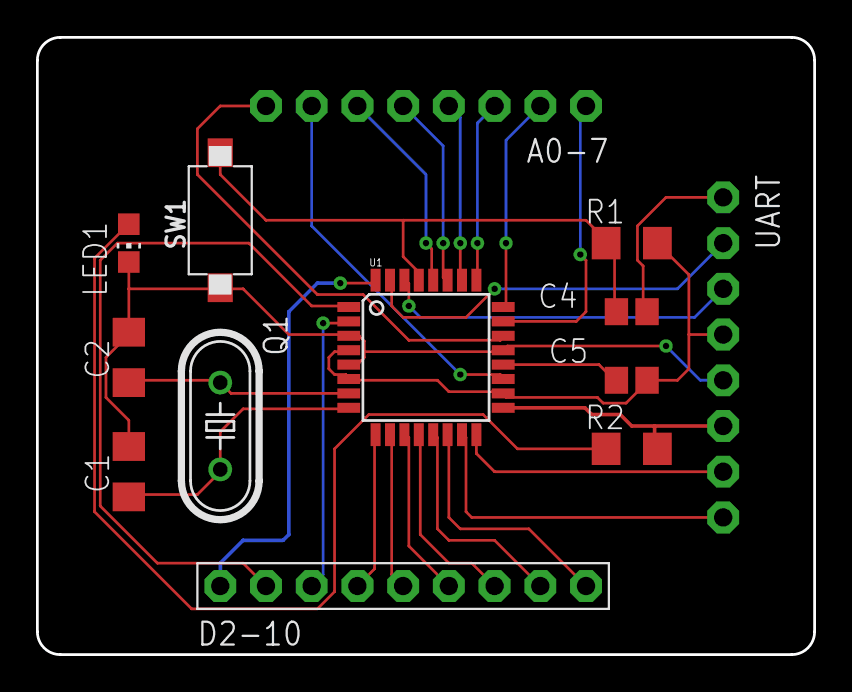
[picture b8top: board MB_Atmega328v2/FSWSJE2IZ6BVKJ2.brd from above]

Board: 2 copper layers, 43.2 x 34.3 mm, 13 parts (0 on the bottom side), 30 nets.

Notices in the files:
parts and their libraries:
SparkFun-Connectors: Licensing: CC v3.0 Share-Alike You are welcome to use this library for commercial purposes.
SparkFun-Passives: Licensing: Creative Commons ShareAlike 4.0 International - https://creativecommons.org/licenses/by-sa/4.0
